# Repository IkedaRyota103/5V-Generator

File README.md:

# 5V-Generator
名前:  
5V発生器  
  
作成者:  
Burglar  
紹介：  
最近エネループをぱちった　　

回路図:  

PCB:  

使用素子:  
USB_B_Female(メス)  
  
XA_1×02_Vertical(縦向き実装)  
  
COM(C接点)Switch  
  
Capacitor(コンデンサ)_定格電圧10V  
  
注意:これらは正式名称ではありません。

CNCフライス使用刃物:  
B_Cu:土左まさのり  

Edge_Cuts:エンドミル0.8mm  

Drill:土佐まさのり  

(Drill_Mill):エンドミル0.8mm  

注意:  
・ドリルとドリルミルはどちらか一方のみにして  
 ください。  
・土佐まさのりのみでは開けれない大きさの穴は  
 ボール盤などで加工してください。

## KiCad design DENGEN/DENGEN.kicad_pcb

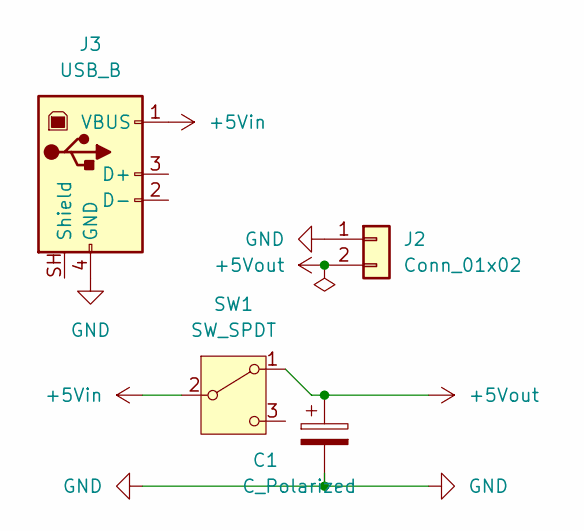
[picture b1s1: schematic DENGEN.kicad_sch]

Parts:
C1: C_Polarized; CP_Radial_D5.0mm_P2.00mm
J2: Conn_01x02; JST_XA_B02B-XASK-1_1x02_P2.50mm_Vertical
J3: USB_B; USB_B_OST_USB-B1HSxx_Horizontal
SW1: SW_SPDT; FanPinHeader_1x03_P2.54mm_Vertical

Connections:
+5Vin: J3.1 (VBUS), SW1.2 (B)
+5Vout: C1.1, J2.2, SW1.1 (A)
GND: C1.2, J2.1, J3.4 (GND)

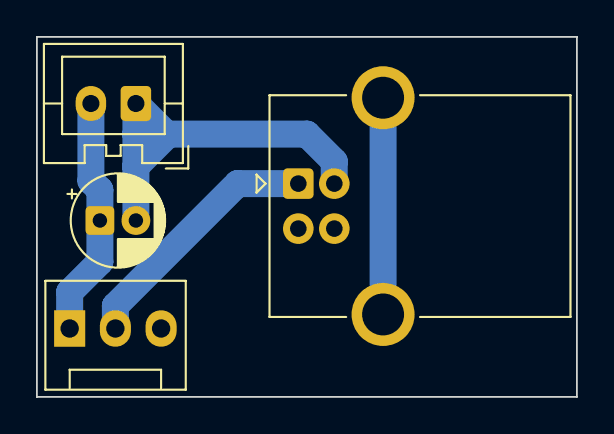
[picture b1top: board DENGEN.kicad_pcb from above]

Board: 2 copper layers, 30.0 x 20.0 mm, 4 parts (0 on the bottom side), 3 nets.

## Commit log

2026-05-13 README.md を更新
